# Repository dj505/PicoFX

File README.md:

# PicoFX
A compact, feature-rich keyboard-style controller for Pump it Up simulators

[See it in action!](https://www.youtube.com/watch?v=75ObKhgJE3M)

## Table of Contents
This readme may be rather large, but don't let that intimiate you! I've included as much information as possible to make sure this build is straightforward and beginner friendly. If you have any questions at all, feel free to shoot me a message through Discord (dj505#6697) or open an issue here.
* [Component List](#components)
* [Ordering the PCBs](#ordering-the-pcbs) (for first time/inexperienced builders)
* [Ordering Components](#ordering-components) (for first time/inexperienced builders)
* [How to Build](#how-to-build)
* [Flashing the Firmware](#flashing-the-firmware)
* [FAQ](#faq)

## Components
Many components listed below are optional. If you prefer to spend as little as possible on this build, they can be entirely omitted. In the case of the FR4 plate, leaving it out will require you to 3D print or laser cut a plate/case.  
All prices below reflect the bare minimum cost of building **5 controllers** with PCBs and components from **JLCPCB and LCSC** respectively, as the minimum number of PCBs from JLCPCB per deisgn is 5. Some components link to AliExpress as it's generally a good, cheap source for keycaps, switches, and other components LCSC won't have, at the cost of long shipping times. It's highly recommended to buy a few extra of each component in case any are damaged, lost, or DOA.

| Components (per 1 controller) | Specs | Notes | Recommended Purchase Link | Approximate Min. Cost (USD, per 5 controllers) |
|-------------------------------|-------|-------|---------------------------|------------------------------------------------|
|1x Raspberry Pi Pico|Any Pico that is **not** the Pico H|No pre-soldered headers. Pico W should work, but there is currently no WiFi or Bluetooth functionality here. This may change in the future. Pin-compatible clones should work (in case you want USB C) - **be sure** that the pin mappings are the same! These are not officially supported and it's up to you to make sure it works.|[Link](https://www.digikey.ca/en/products/detail/raspberry-pi/SC0915/13624793)|$4|
|Pin Headers|2 rows of 20 headers|The Pico has 20 pins on either side. You can either go with 1 strip of 20 per side or 2 strips of 10 per side, whichever comes out cheaper and occupies all pins.|[Link](https://www.ebay.ca/itm/165633656340)|$12|
|1x 3D printed shell|N/A|Cost depends on whether or not you own a 3D printer (or know someone who does) and what service you use.|N/A - STL file located in `Case/3D Prints` directory|N/A|
|2x right angle tactile switches|Approx. 7.5x6mm, right angle. See recommended purchase link|Recommendation - buy a couple extras just in case.|[Link](https://www.lcsc.com/product-detail/Tactile-Switches_C-K-PTS645VL392LFS_C285523.html)|$0.96|
|10x keyboard switches|Must be Cherry MX compatible|The ones linked here are what I used personally for the sake of a price estimate. You can pick any kind of switch you want. Ensure the switches you choose will accommodate the LEDs you pick!|[Link](https://www.aliexpress.com/item/1005003810967081.html)|$23.99|
|10x keycaps|Must be Cherry MX compatible|Ideally a "flat" or uniform profile like DSA, XDA, F10, etc. Recommendation - source these on your own for better quality and prices.|[Link](https://www.aliexpress.com/item/32830177884.html)|$28.50|
|4x machine screws|M3 **or** M3.5\*8mm, pan head|Black would look nice if you can source some. Countersunk screws will not sit flush, and it's not advisable to countersink fiberglass without amazing ventilation and a mask with filters. M3 or M3.5 depends on your printer and its tolerances, but the design was made with M3.5 in mind. Recommendation - buy a couple extras just in case.|[Link](https://www.aliexpress.com/item/32811037821.html)|$1.45|
|**(OPTIONAL)** 10x LEDs|4x red, 4x blue, 2x yellow (or whichever colours you prefer tbh)|LEDs should be 3mm or smaller to fit your switches! Recommendation - source these yourself or find alternatives through LCSC. Buy a couple extras just in case.|[Link](https://www.aliexpress.com/item/32685621460.html)|$3.29|
|10x resistors|Surface mount, 330Ohm, 0805 package|Only needed if using the above LEDs. Recommendation - buy a ton of them. They cost fractions of a cent each, and they're easy to lose!|[Link](https://www.lcsc.com/product-detail/Chip-Resistor-Surface-Mount_UNI-ROYAL-Uniroyal-Elec-0805W8F3300T5E_C17630.html)|$0.17|
|**(OPTIONAL)** 6x WS2812B LEDs\*|Must be WS2812**B** or pin-compatible. Earlier WS2812 (non-B) LEDs with 6 pins will not work.|Used for underglow lighting. **Definitely** buy extras - they're somewhat delicate and easy to break or burn out by mistake during installation.|[Link](https://www.lcsc.com/product-detail/Light-Emitting-Diodes-LED_Worldsemi-WS2812B-B-W_C2761795.html)|$4.43|
|1x Main PCB|1.6mm thickness, lead-free HASL or ENIG finish recommended|Estimated price based on default options, but with a **lead-free HASL finish**.|[Link](https://cart.jlcpcb.com/quote?orderType=1&stencilLayer=2&stencilWidth=100&stencilLength=100&stencilCounts=5) - gerber.zip located in `gerber` directory|$8.40|
|**(OPTIONAL but recommended)** 1x FR4 plate|1.6mm thickness, lead-free HASL finish recommended|Estimated price based on default options, but with a **lead-free HASL finish**. Not enough contacts or mask artwork to justify ENIG finish.|[Link](https://cart.jlcpcb.com/quote?orderType=1&stencilLayer=2&stencilWidth=100&stencilLength=100&stencilCounts=5) - gerber.zip located in `Case/Plate/gerber` directory|$9.30|
|_**Total Cost**_||This cost estimate reflects building **5 full PicoFX controllers**. If you're splitting the cost through a group buy, divide it by the number of people participating.||$96.89|

\* There are a few options for RGB underglow depending on your needs and experience.  
- Option 1: There are foorprints for 6 individual WS2812B LEDs **(PLCC4, 5x5mm)** around the perimiter of the case. There are hand-solder friendly 0805 capacitor footprints beside each LED, but these are only needed if you run into issues with the LEDs being unstable or acting erratically. This option will likely look nicer, but may be more difficult for beginners to solder.
- Option 2: A regular WS2812B strip cut down to 6 LEDs in length can be soldered to the three pins on the left hand side of the board (from the back) and adhered along the length of the PCB. This option is more friendly to beginners or those who aren't as confident with SMD soldering, but the lighting it provides isn't quite as even. **Requires jumping the "Strip Enable" pad.**

If you have any questions about the parts requirements, costs, or sourcing components, feel free to shoot me a message through Discord (dj505#6697) or open an issue here.

## Ordering the PCBs
If you've never ordered PCBs before, don't worry! The process is super simple on most websites. These instructions are here to make sure each step is clear and straightforward, and to avoid accidentally ordering a set of boards with the wrong options. Keep in mind, most manufacturers have a **minimum order number of 3-5**, which means you're going to need to order at least 3-5 of each PCB (main board and plate). Feel free to put together a group order with friends or sell the extras! I really don't mind others making and selling units, just make sure they're well made, thoroughly tested, and work properly (and consider [donating a couple bucks](https://ko-fi.com/dj505piu) if you can!)
Here are my recommendations:
| Manufacturer | Minimum order number | Notes |
|--------------|----------------------|-------|
|PCBWay        |5 PCBs per design     |Has sponsored the PicoFX, however opinions expressed are 100% my own. Offers several discount coupons for new users (first time order discount, coupons for completing a profile, etc). Straightforward order process, excellent quality end result. Also offers 3D printing, CNC, and PCB assembly, if needed. Recommended.|
|JLCPCB        |5 PCBs per design     |Provides new user discounts. Straightforward order process, high quality end result. Also offers 3D printing and PCB assembly, if needed. Recommended.|
|OSH Park      |3 PCBs per design     |Fewer options than the above two, but the minimum order number is smaller. Colour options are limited to purple and "after dark", a clear solder mask over black substrate so all the traces are visible (very cool but not very visible for this project). Overall a bit more costly, but shipping is generally faster as they're based in the United States.|

Some manufacturers may need you to manually specify the PCB dimensions. To save you some time, here are the dimensions for both PCBs:
| PCB | Width | Height |
|-----|-------|--------|
|Main board|120.7|70.6 mm|
|Plate|139.1 mm|77.2 mm|

The example order process described here is written with PCBWay in mind, but applies to most manufacturers. Be sure to sign up for an account beforehand and set up your delivery address/etc so you're good to go when you order.
1. Download the gerber(s) you plan to order. Check the [releases](https://github.com/dj505/PicoFX/releases) page for the gerber zip files. **None of the other files are needed - just the zip files.**
2. Visit the manufacturer's website and look for the "Quote Now" button. Choose the settings for and add both PCBs to your cart individually and order them together once they're in there.
3. Punch in the necessary options. The majority of these don't need to be changed and you can leave them be, however I recommend making sure the following are correct for **both** PCBs:
    * PCB thickness: 1.6mm
    * Surface Finish: LeadFree HASL **OR** ENIG (gold finish, more expensive but really cool and higher quality, but only recommended for the main PCB as the plate doesn't have enough solder points to warrant it)
        * HASL (with lead) can be used but I personally try to avoid it. Up to you.
    * Copper Weight: 1oz
    * You can pick whichever solder mask colour you want - this is the colour your final boards will appear. If you want, you can have different colours for the main PCB and the plate! Just remember that the main PCB may not be visible except from the bottom, if the case you use is transparent.
4. **Recommended, but optional** - For the main board, you may add a note to the order to clarify that one of the design choices used by the keyboard switch footprint is intentional. The top layer's solder points are covered by solder mask to give it a cleaner look, as no soldering will ever be done on that side. You can either specify this as a note when submitting the order or wait to be asked about it and explain then. PCBWay manufactured the files as provided without bringing it up, but JLCPCB contacted me to double check. Your mileage may vary.
5. Once you have your desired orders ready in your cart, the rest of the process is identical to any other online shopping site. Pick your shipping option, pay, and you're good to go!

## Ordering Components
To make sourcing a little easier and cheaper, you can find all the small components for this project on [LCSC](https://lcsc.com). This doesn't include more specialized or larger parts such as keyboard switches, or hardware such as keycaps or screws. Check the recommended purchase links for those, or source them from sites like eBay, AliExpress, etc.  
The bare minimum numbers of each part per controller are listed below, but I would **highly recommend** ordering a few extras of each, as they're very small and can be easily lost or damaged. Thankfully they're very inexpensive and adding extras will only cost you a few cents to a dollar more. See the [Components section](#components) for a recap of what is/isn't optional and the alternatives for each.  
* 6 x [WS2812B RGB LED](https://lcsc.com/product-detail/Light-Emitting-Diodes-LED_Worldsemi-WS2812B-B-W_C2761795.html) (3 extra recommended per controller)
* 10 x [0805 330ohm SMD resistor](https://lcsc.com/product-detail/Chip-Resistor-Surface-Mount_UNI-ROYAL-Uniroyal-Elec-0805W8F3300T5E_C17630.html) (5 extra recommended per controller but they're so cheap you can order literally hundreds for well under a dollar total)
* 2 x [right angle tactile switches](https://lcsc.com/product-detail/Tactile-Switches_C-K-PTS645VL392LFS_C285523.html) (1 extra recommended per controller at most, they're super easy to solder but it would suck if one arrived damaged or DOA)

## How To Build
This build applies to the **full materials list**, including the FR4 plate and surface mount parts. Text descriptions will be provided for the optional alternatives, such as replacing SMD LEDs with LED strips or skipping the FR4 plate. Be sure to read through each step in its entirety before doing anything!

**[Build process & guide video](https://youtu.be/5a2lHV3uc5E)** on YouTube

1. **Solder the WS2812B LEDs in place.** If using an LED strip, skip this step and wait until step 9. The notch present on each LED should be positioned on the bottom right side. These can be finicky to solder - don't heat them for too long!

2. **Solder the SMD resistors in place.** The footprints used for these are made with hand soldering in mind, but if you have a hot air rework station, reflow oven, or any other fancy tools at your disposal, those work great too. If you don't feel comfortable soldering these, you *can* skip them and bridge the pads with solder, but it's not good practice.

3. **Solder in the pin headers.** It doesn't really matter which orientation you use, but if you insert the **short** pins through the PCB (unlike what I did here) you can avoid some extra trimming. Inserting the long side through the PCB will require trimming on the other side to make sure there's enough clearance to mount the switches. **Do NOT solder the Pico yet.** Optionally, if you don't have pin headers, you can use diole legs instead, or skip this step entirely and surface mount the Pico. This is not recommended, however, beacuse it may require trimming the switch step to ensure there's clearance, and absolutely requires trimming the LED/switch legs flush. Do this at your own risk.

4. **If using the FR4 plate, solder in the other, smaller pin headers.** These go on the **FRONT** side of the board and connect with the top plate, so make sure the **long** side is facing up, as shown.

5. **Mount the switches in the plate. Mount the plate on the main PCB.** Before you solder, make sure no legs are bent under the PCB and all of them are poking through the solder pads. Also insert and solder the LEDs one at a time. Pro tip - test your LEDs and make sure that they both work and are the right colour before soldering them in! The longer leg (positive) is marked "+" with a round hole, and the shorter leg (negative) is marked "-" with a square hole. **Note: if your switches require LEDs to be mounted underneath, make sure to insert those first.**

6. **Solder the test and service buttons.** If you **are** using the FR4 plate, make sure you solder these to the holes on the plate as shown below. In either configuration, the switches should end up on the bottom of the PCB, not sticking out the top. To avoid sharp solder spikes, consider trimming the legs flush before soldering.

7. **Solder the pin headers for the test and service buttons** if you haven't done so already. As with the previous step, consider trimming the pins flush before soldering to avoid sharp solder spikes.

8. **Install the Raspberry Pi Pico.** The fun part! Simply place it on the pin headers and solder each pin in place.

9. **If you didn't surface mount solder the WS2812B LEDs and opted for a strip**, cut the strip to a length of 6 LEDs. You may need to trim the legs of the LEDs along the bottom of the board so the LED strip can sit flat and stick properly. Jump the 2 pads labelled "Strip Enable" with a blob of solder, and wire up the LED strip to the corresponding pads. Ensure you're soldering to the "DI" or "DIN" pin on the LED strip! If you solder to "DO" or "DOUT" then your LEDs will not light up. (Note: lengths longer than 6 LEDs will work but may exceed the standard USB 500mA current draw and will require changes to the firmware.)

You're done! Flash the firmware, install the bottom half of the case, and you're good to go.

## Flashing the Firmware

[**Prebuilt PIUIO firmwares here!**](https://github.com/48productions/piuio-pico/releases/tag/v1.0.0)

[**Prebuilt HID gamepad/keyboard firmware here!**](https://github.com/dj505/Pico-Game-Controller-PicoFX/releases/tag/v1.0.0)

For the PIUIO firmware source, see the [piuio-pico](https://github.com/48productions/piuio-pico/) repository by [48productions](https://github.com/48productions). This firmware emulates a PIUIO board and can be used on Windows devices via IO2Key ([helpful installation video](https://www.youtube.com/watch?v=xo5m9dlNFfY) by Nirvash) or on Linux via a [custom kernel driver](https://github.com/DinsFire64/piuio) (installation instructions in the README).

### ***Do not*** use this firmware on any hand controller to play the latest official game online! It is considered cheating. Your machine and piugame profile will be banned, and you yorself can be banned from official events. Using any aspect of this project for prohibitied play on officially supported games is not endorsed, encouraged, or supported. However, do feel free to use this firmware to build a proper dance pad for legitimate play.

If you plan to use this controller with simulators exclusively, see the HID gamepad/keyboard firmware linked above.

To install the firmware, plug in your Raspberry Pi Pico while holding the "BOOTSEL" button to put it in programming mode. It should show up as a USB mass storage device. Compile the firmware (if necessary) and copy the .uf2 file onto the Pico through the file explorer. It should automatically disconnect itself and restart. You're done!

## FAQ
* Can I make and sell these, or sell extras?
    * Go ahead! However, do make sure they're well built and thoroughly tested, and consider [donating a few bucks](https://ko-fi.com/dj505piu) if you can!
* Does this work with official games?
    * Yes, **however** using a hand controller on any currently online and supported game (XX 20th Anniversary Edition and Phoenix at the time of writing) is considered cheating, especially during events. Hand controller play **can** be detected and you may get the game/machine banned or blacklisted alongside your piugame account, and you may also be banned from official events. Not worth the risk!
* Can I make this without any LEDs to start with and add them later?
    * Mostly. There is one in-switch LED that won't be reachable once the Pico is soldered in. If you plan to add LEDs later on, either install sockets of some kind to account for this without needing to solder later, or install the Pico with male/female pin headers so you can remove it later to install LEDs. All RGB underglow LEDs can be soldered at any time without removing the Pico.
* How do I make the underglow work?
    * If you're using this controller's PIUIO firmware with IO2Key on Windows for StepF2/StepP1/StepPrime/StepPXX, underglow lighting will not work. Base StepMania or Project OutFox support lighting but extra manual configuration will need to be done, which I haven't had a chance to try yet. Linux users running StepMania or Project OutFox can use the kernel driver linked in [Flashing the Firmware](#flashing-the-firmware) for lighting support by editing Preferences.ini and editing the `LightsDriver` line to read `LightsDriver=PIUIO_Leds`. If you're using the gamepad firmware, underglow lighting will be on by default and does not react to the game.
* Can I make this project USB C compatible somehow?
    * If you can find a Pico clone that uses USB C and is pin-compatible with the official Raspberry Pi Pico, you absolutely can. I can't provide official support for multiple boards though, otherwise this project would get really messy really fast.
* Can I build one of these without a PCB?
    * Absolutely! Check out the "3D Prints" folder for 3D printable cases and plates. Be prepared to do a lot of tedious wire management and soldering, though! You'll also need to figure out how to mount the test and service buttons on your own.
* Can I make a hotswappable PicoFX?
    * While there is no footprint for Kailh hotswap sockets or anything similar, you can technically use MillMax sockets. I wouldn't recommend it unless you really know what you're doing, though. It took me an hour to install the sockets alone, and I ruined three. This also makes LEDs complicated. Hotswap sockets for LEDs exist, but you could also try to solder surface mount LEDs to the through-hole pads if you want. I don't provide official support with this method but I do encourage you to get creative :) Maybe a future hardware revision will account for this.

## Special Thanks
Thanks to
- therathatter & 48productions (firmware things)
- SpaghettiSnail (putting up with my KiCad woes)
- BedrockSolid (KiCad and component sourcing advice)
- Everyone else who supported and contributed to the project!

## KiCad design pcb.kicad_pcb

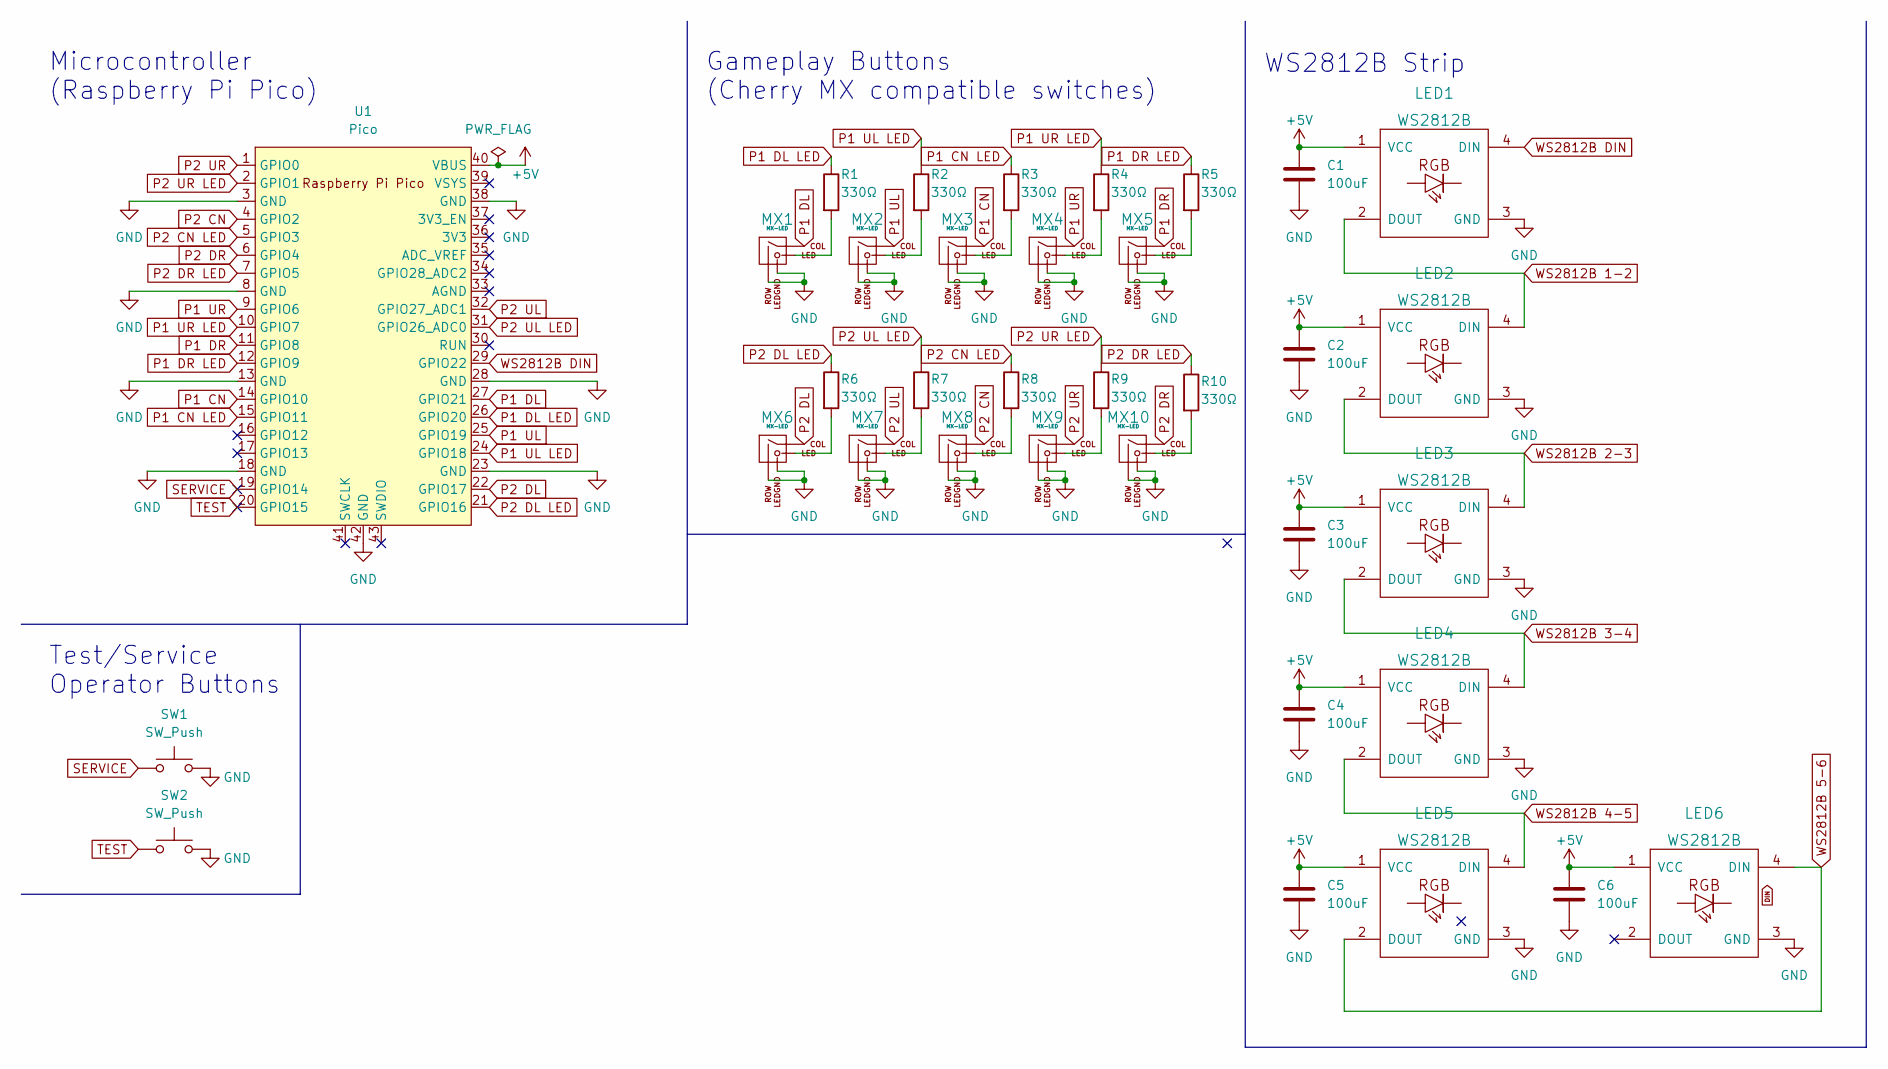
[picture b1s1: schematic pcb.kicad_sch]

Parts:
C1, C2, C3, C4, C5, C6: 100uF; C_0805_2012Metric_Pad1.18x1.45mm_HandSolder
LED1, LED2, LED3, LED4, LED5, LED6: WS2812B; LED_WS2812B_PLCC4_5.0x5.0mm_P3.2mm; LCSC C2761795
MX1, MX2, MX3, MX4, MX5, MX6, MX7, MX8, MX9, MX10: MX-LED; MX-Alps-Choc-1U
R1, R2, R3, R4, R5, R6, R7, R8, R9, R10: 330Ω; R_0805_2012Metric_Pad1.20x1.40mm_HandSolder; LCSC C17630
SW1, SW2: SW_Push; SW_PUSH_6mm
U1: Pico; RPi_Pico_SMD_TH

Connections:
+5V: C1.1, C2.1, C3.1, C4.1, C5.1, C6.1, LED1.1 (VCC), LED2.1 (VCC), LED3.1 (VCC), LED4.1 (VCC), LED5.1 (VCC), LED6.1 (VCC), U1.40 (VBUS)
GND: C1.2, C2.2, C3.2, C4.2, C5.2, C6.2, LED1.3 (GND), LED2.3 (GND), LED3.3 (GND), LED4.3 (GND), LED5.3 (GND), LED6.3 (GND), MX1.2 (ROW), MX1.4 (LEDGND), MX2.2 (ROW), MX2.4 (LEDGND), MX3.2 (ROW), MX3.4 (LEDGND), MX4.2 (ROW), MX4.4 (LEDGND), MX5.2 (ROW), MX5.4 (LEDGND), MX6.2 (ROW), MX6.4 (LEDGND), MX7.2 (ROW), MX7.4 (LEDGND), MX8.2 (ROW), MX8.4 (LEDGND), MX9.2 (ROW), MX9.4 (LEDGND), MX10.2 (ROW), MX10.4 (LEDGND), SW1.2, SW2.2, U1.3 (GND), U1.8 (GND), U1.13 (GND), U1.18 (GND), U1.23 (GND), U1.28 (GND), U1.38 (GND), U1.42 (GND)
unnamed: MX1.3 (LED), R1.2
unnamed: MX2.3 (LED), R2.2
unnamed: MX3.3 (LED), R3.2
unnamed: MX4.3 (LED), R4.2
unnamed: MX5.3 (LED), R5.2
unnamed: MX6.3 (LED), R6.2
unnamed: MX7.3 (LED), R7.2
unnamed: MX8.3 (LED), R8.2
unnamed: MX9.3 (LED), R9.2
unnamed: MX10.3 (LED), R10.2
P1 CN: MX3.1 (COL), U1.14 (GPIO10)
P1 CN LED: R3.1, U1.15 (GPIO11)
P1 DL: MX1.1 (COL), U1.27 (GPIO21)
P1 DL LED: R1.1, U1.26 (GPIO20)
P1 DR: MX5.1 (COL), U1.11 (GPIO8)
P1 DR LED: R5.1, U1.12 (GPIO9)
P1 UL: MX2.1 (COL), U1.25 (GPIO19)
P1 UL LED: R2.1, U1.24 (GPIO18)
P1 UR: MX4.1 (COL), U1.9 (GPIO6)
P1 UR LED: R4.1, U1.10 (GPIO7)
P2 CN: MX8.1 (COL), U1.4 (GPIO2)
P2 CN LED: R8.1, U1.5 (GPIO3)
P2 DL: MX6.1 (COL), U1.22 (GPIO17)
P2 DL LED: R6.1, U1.21 (GPIO16)
P2 DR: MX10.1 (COL), U1.6 (GPIO4)
P2 DR LED: R10.1, U1.7 (GPIO5)
P2 UL: MX7.1 (COL), U1.32 (GPIO27_ADC1)
P2 UL LED: R7.1, U1.31 (GPIO26_ADC0)
P2 UR: MX9.1 (COL), U1.1 (GPIO0)
P2 UR LED: R9.1, U1.2 (GPIO1)
SERVICE: SW1.1, U1.19 (GPIO14)
TEST: SW2.1, U1.20 (GPIO15)
WS2812B 1-2: LED1.2 (DOUT), LED2.4 (DIN)
WS2812B 2-3: LED2.2 (DOUT), LED3.4 (DIN)
WS2812B 3-4: LED3.2 (DOUT), LED4.4 (DIN)
WS2812B 4-5: LED4.2 (DOUT), LED5.4 (DIN)
WS2812B 5-6: LED5.2 (DOUT), LED6.4 (DIN)
WS2812B DIN: LED1.4 (DIN), U1.29 (GPIO22)

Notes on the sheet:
Gameplay Buttons (Cherry MX compatible switches)
Microcontroller (Raspberry Pi Pico)
Test/Service Operator Buttons
WS2812B Strip

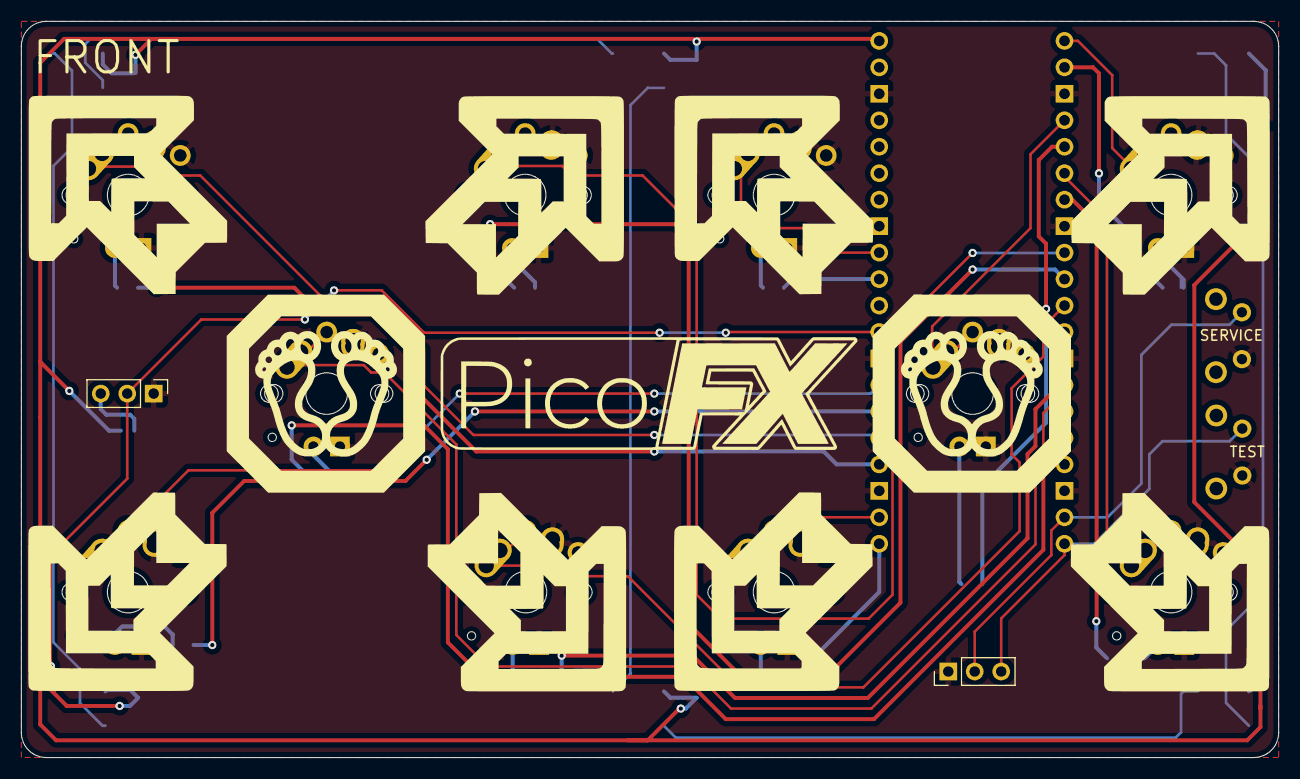
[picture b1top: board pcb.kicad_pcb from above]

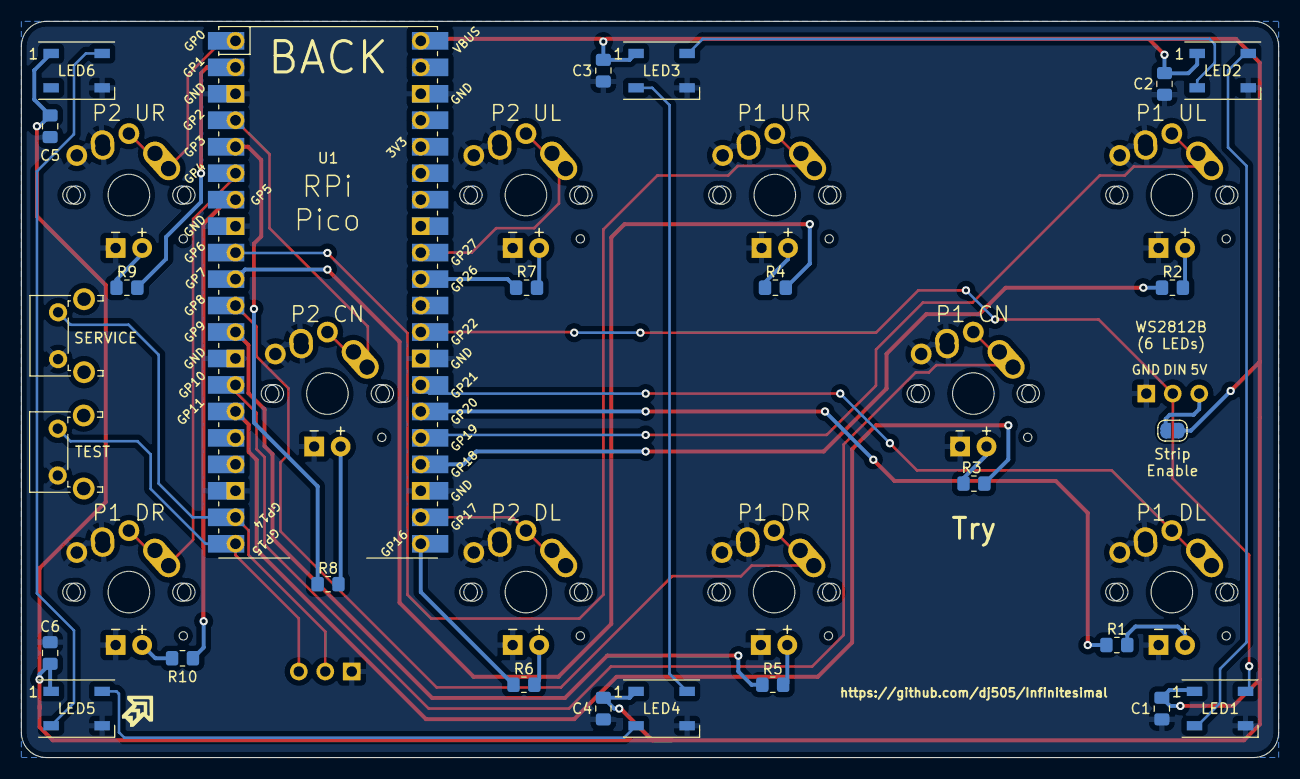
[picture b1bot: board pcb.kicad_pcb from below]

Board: 2 copper layers, 120.7 x 70.6 mm, 33 parts (23 on the bottom side), 38 nets.

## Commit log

2022-10-13 Add KiCad files
2022-10-13 add submodules for footprints
2022-10-13 Add footprint libraries
2022-10-13 Finish schematic, add WS2812B submodule/footprint
2022-10-13 Footprint assignment
2022-10-13 Initial PCB layout
2022-10-13 P2 initial routing done
2022-10-13 Update P2 routing (this is hard D:)
2022-10-14 P1 initial routing, no more WS2812Bs built in
2022-10-14 WS2812B strip connector routing
2022-10-14 Ground fill
2022-10-14 Design rule and minor positioning fixes
2022-10-14 Final touches for Rev 1
2022-10-14 Create LICENSE
2022-10-14 Add Rev 1 gerbers
2022-10-16 Fixed front solder mask covering pads
2022-10-16 Un-fix front mask (it's meant to be like that)
2022-10-16 ooooo fancy pcb art (+ silkscreen adjustments)
2022-10-16 More PCB art, some tweaking
2022-10-17 Clean up schematic, PCB adjustments
2022-10-17 add test/service buttons (oops)
2022-10-17 actually add test/service buttons (double oops)
    position not final
2022-10-17 update gerbers
2022-10-17 Remove Pico USB holes, silkscreen fixes
2022-10-19 Tidy up schematic more
2022-10-19 Clean up trace routing
2022-10-24 Add resistors to LEDs, general cleanup/updates
2022-10-24 nitpicks
2022-10-24 bonus nitpick
2022-10-24 Update gerbers, extra nitpicks
2022-10-24 Move R8 to allow for surface mounting the Pico
    Not recommended, but you can if you really want to now. Also updated the design rules to fit JLCPCB manufacturing specs.
2022-10-25 we only want 8 WS2812Bs
2022-10-26 Add WS2812B footprints, various tweaks
2022-10-26 Fix 1 typo
2022-10-27 Add FR4 plate design (with logo!)
2022-10-27 Add test/service buttons to plate, begin renaming
2022-10-27 Use 90 degree buttons for test/service, smol fixes
2022-10-27 Final PCB changes for now. See description
    Not making even a single change to either PCB until I receive the initial batch and thoroughly test everything. If any changes need to be made, they'll be made then. README and such will continue to 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
2022-10-30 Fix P1 UL/DL being swapped
2022-11-17 Update Instructions
2022-11-17 Fic Readme
2022-11-17 Final instructions fix I hope
2022-11-17 welp
2022-11-17 Big readme update
2022-11-17 Small readme update
2022-11-17 Slowly learning to preview readme changes
2022-11-23 terminology is hard
2022-11-29 Add 3D printable case/plate files
2022-11-29 Update components list
2022-11-29 Move 3D prints to "Case" directory
2022-11-30 Update parts list table
2022-11-30 smol typo
2022-11-30 Update "Ordering components" section
2022-11-30 Capitalization oops
2022-12-12 Add pin headers to parts list
2023-01-13 Update README photo & PCB order instructions
2023-02-07 Add keeb.io Alps+Choc+MX footprint
2023-02-07 Clearance fixes, update text to rev. 4
